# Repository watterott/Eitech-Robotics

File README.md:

# Eitech Robotics
Eitech Robotics is an Microchip SAMW25 based open-source robotics board.

* [Microchip ATSAMW25](http://www.microchip.com/wwwproducts/en/ATSAMW25) Module (SAM D21 ARM Cortex-M0+ and WINC1500 WiFi/WLAN SoC)
* USB CDC+MSC Bootloader (Arduino compatible)
* 5V tolerant IOs, UART, SPI, I2C
* 2x Dual Full-Bridge Motor Drivers (Allegro Micro A3909, up to 1A per Phase)
* 5V Switching Regulator (up to 2A)

## Hardware and Software
* [Schematics/Layout](https://github.com/watterott/Eitech-Robotics/tree/master/hardware)
* [Board Support Package for Arduino IDE](https://github.com/watterott/Eitech-Robotics/tree/master/arduino#eitech-board-support-package)
* [Driver for Windows](https://github.com/watterott/Eitech-Robotics/raw/master/arduino/driver.zip)

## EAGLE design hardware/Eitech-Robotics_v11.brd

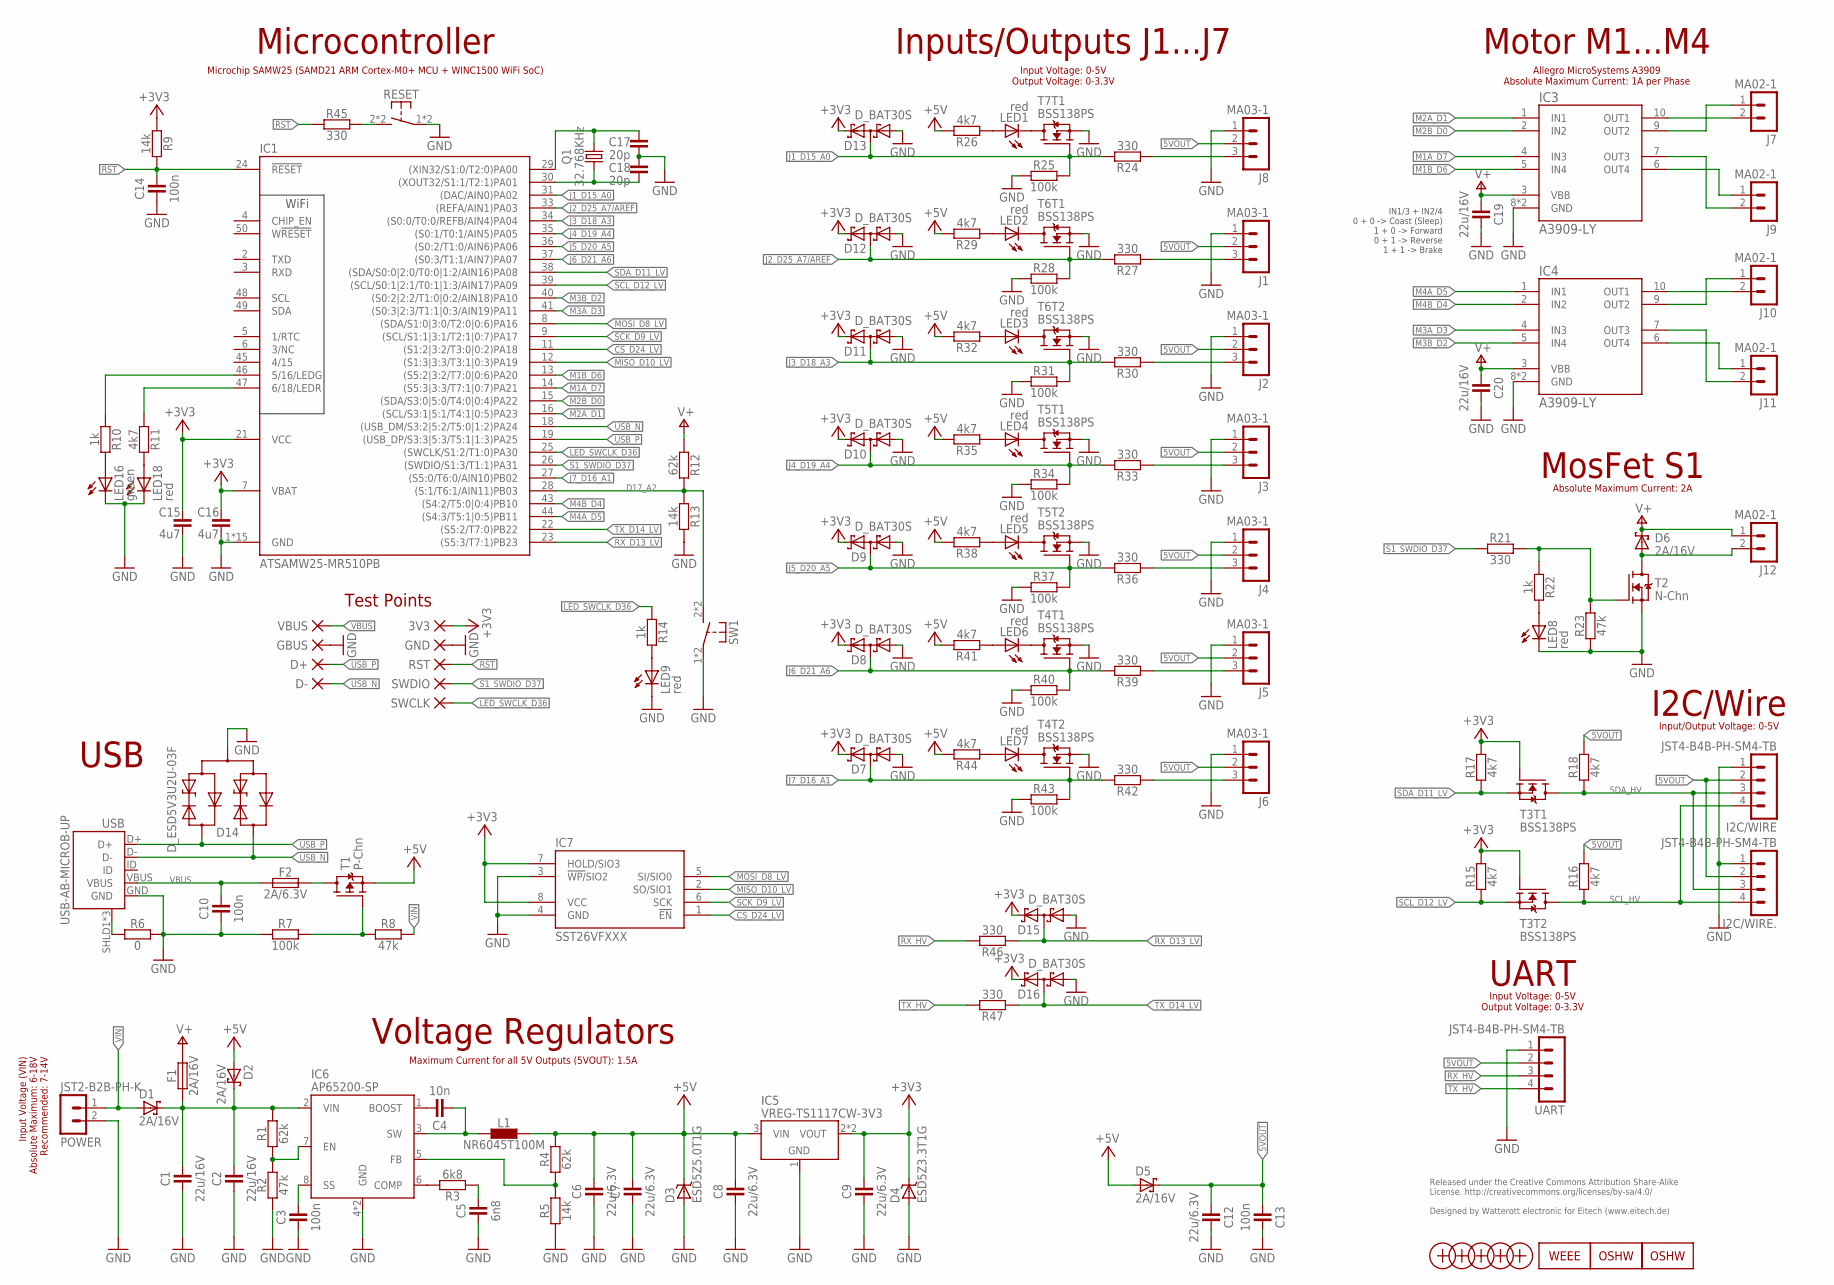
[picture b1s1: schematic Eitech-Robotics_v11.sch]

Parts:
3V3: PAD-1.0_NC
C1, C2, C19, C20: 22u/16V; C0805
C3, C10, C13, C14: 100n; C0402
C4: 10n; C0402
C5: 6n8; C0402
C6, C7, C8, C9, C12: 22u/6.3V; C0805
C15, C16: 4u7; C0603
C17, C18: 20p; C0402
D1, D2, D5, D6: 2A/16V; SOD123
D3: ESD5Z5.0T1G; SOD523
D4: ESD5Z3.3T1G; SOD523
D7, D8, D9, D10, D11, D12, D13, D15, D16: D_BAT30S; SOT323
D14: D_ESD5V3U2U-03F; SOT723
D+: PAD-1.0_NC
D-: PAD-1.0_NC
F1: 2A/16V; C1812
F2: 2A/6.3V; C1206
GBUS: PAD-1.0_NC
GND: PAD-1.0_NC
I2C/WIRE, I2C/WIRE.: JST4-B4B-PH-SM4-TB; JST_B4B-PH-SM4-TB
IC1: ATSAMW25-MR510PB; ATSAMW25-MRX10
IC3, IC4: A3909-LY; MSOP10-PAD
IC5: VREG-TS1117CW-3V3; SOT223
IC6: AP65200-SP; SO08-PAD
IC7: SST26VFXXX; SO08
J1, J2, J3, J4, J5, J6, J8: MA03-1
J7, J9, J10, J11, J12: MA02-1
L1: NR6045T100M; L_NR60XX
LED1, LED2, LED3, LED4, LED5, LED6, LED7, LED8, LED9, LED18: red; C0603
LED16: green; C0603
LOGO1: OSHW_LOGOX0100; OSHW_6X100
LOGO2: OSHW_LOGOX0150; OSHW_6X150
LOGO4: WEEE_LOGO-S; WEEE_TPLAC_S
POWER: JST2-B2B-PH-K; JST_B2B-PH-K
Q1: 32.768KHz; CRYSTAL_ZM315
R1, R4, R12: 62k; C0402
R2, R8, R23: 47k; C0402
R3: 6k8; C0402
R5, R9, R13: 14k; C0402
R6: 0; C0402
R7, R25, R28, R31, R34, R37, R40, R43: 100k; C0402
R10, R14, R22: 1k; C0402
R11, R15, R16, R17, R18, R26, R29, R32, R35, R38, R41, R44: 4k7; C0402
R21, R24, R27, R30, R33, R36, R39, R42, R45, R46, R47: 330; C0402
RESET: SW-TACTILE-TL3305C; TL3305; MPN TL3305C
RST: PAD-1.0_NC
SW1: SW-TACTILE-TL3305C; TL3305; MPN TL3305C
SWCLK: PAD-1.0_NC
SWDIO: PAD-1.0_NC
T1: P-Chn; SOT23
T2: N-Chn; SOT23
T3, T4, T5, T6, T7: BSS138PS; SOT363
UART: JST4-B4B-PH-SM4-TB; JST_B4B-PH-SM4-TB
USB: USB-AB-MICROB-UP; USB-MICROB-1051330011
VBUS: PAD-1.0_NC
X1, X2, X3, X4: PASSER-07; PASSER_07MM
X5: PASSER-04; PASSER_04MM

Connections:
5VOUT: C12.2, C13.2, D5.C, I2C/WIRE.2, I2C/WIRE..2, J1.2, J2.2, J3.2, J4.2, J5.2, J6.2, J8.2, R16.2, R18.2, UART.2
+3V3: 3V3.1, C9.2, C15.2, C16.2, D4.C, D7.2 (C), D8.2 (C), D9.2 (C), D10.2 (C), D11.2 (C), D12.2 (C), D13.2 (C), D15.2 (C), D16.2 (C), IC1.7 (VBAT), IC1.21 (VCC), IC5.2 (VOUT), IC5.4 (VOUT), IC7.7 (HOLD/SIO3), IC7.8 (VCC), R9.1, R15.2, R17.2, T3.2 (G), T3.5 (G)
+5V: C6.2, C7.2, C8.2, D2.A, D3.C, D5.A, IC5.3 (VIN), L1.2, R4.2, R26.2, R29.2, R32.2, R35.2, R38.2, R41.2, R44.2, T1.2 (S)
BOOST: C4.2, IC6.1 (BOOST)
COMP: IC6.6 (COMP), R3.2
CS_D24_LV: IC1.11 ((S1:2|3:2/T3:0|0:2)PA18), IC7.1 (!EN)
D17_A2: IC1.28 ((S:1/T6:1/AIN11)PB03), R12.2, R13.1, SW1.2 (S1), SW1.3 (S1)
GND: C1.1, C2.1, C3.1, C5.1, C6.1, C7.1, C8.1, C9.1, C10.1, C12.1, C13.1, C14.1, C15.1, C16.1, C17.2, C18.2, C19.2, C20.2, D3.A, D4.A, D7.1 (A), D8.1 (A), D9.1 (A), D10.1 (A), D11.1 (A), D12.1 (A), D13.1 (A), D14.3 (A), D15.1 (A), D16.1 (A), GBUS.1, GND.1, I2C/WIRE.1, I2C/WIRE..1, IC1.1 (GND), IC1.10 (GND), IC1.17 (GND), IC1.20 (GND), IC1.32 (GND), IC1.42 (GND), IC1.51 (GND), IC1.GND@1 (GND), IC1.GND@2 (GND), IC1.GND@3 (GND), IC1.GND@4 (GND), IC1.GND@5 (GND), IC1.GND@6 (GND), IC1.GND@7 (GND), IC1.GND@8 (GND), IC3.8 (GND), IC3.TP (GND), IC4.8 (GND), IC4.TP (GND), IC5.1 (GND), IC6.4 (GND), IC6.TP (GND), IC7.3 (!WP/!SIO2), IC7.4 (GND), J1.1, J2.1, J3.1, J4.1, J5.1, J6.1, J8.1, LED8.C, LED9.C, LED16.C, LED18.C, POWER.2, R2.1, R5.1, R6.1, R7.1, R13.2, R23.1, R25.1, R28.1, R31.1, R34.1, R37.1, R40.1, R43.1, RESET.1, RESET.4 (P1), SW1.1, SW1.4 (P1), T2.2 (S), T4.1 (S), T4.4 (S), T5.1 (S), T5.4 (S), T6.1 (S), T6.4 (S), T7.1 (S), UART.1, USB.GND
IO16: IC1.46 (5/16/LEDG), R10.1
IO18: IC1.47 (6/18/LEDR), R11.1
J1_D15_A0: D13.3 (CA), IC1.31 ((DAC/AIN0)PA02), R24.2, R25.2, T7.2 (G)
J2_D25_A7/AREF: D12.3 (CA), IC1.33 ((REFA/AIN1)PA03), R27.2, R28.2, T6.2 (G)
J3_D18_A3: D11.3 (CA), IC1.34 ((S0:0/T0:0/REFB/AIN4)PA04), R30.2, R31.2, T6.5 (G)
J4_D19_A4: D10.3 (CA), IC1.35 ((S0:1/T0:1/AIN5)PA05), R33.2, R34.2, T5.2 (G)
J5_D20_A5: D9.3 (CA), IC1.36 ((S0:2/T1:0/AIN6)PA06), R36.2, R37.2, T5.5 (G)
J6_D21_A6: D8.3 (CA), IC1.37 ((S0:3/T1:1/AIN7)PA07), R39.2, R40.2, T4.2 (G)
J7_D16_A1: D7.3 (CA), IC1.27 ((S5:0/T6:0/AIN10)PB02), R42.2, R43.2, T4.5 (G)
LED_SWCLK_D36: IC1.25 ((SWCLK/S1:2/T1:0)PA30), R14.1, SWCLK.1
M1A_D7: IC1.14 ((S5:3|3:3/T7:1|0:7)PA21), IC3.4 (IN3)
M1B_D6: IC1.13 ((S5:2|3:2/T7:0|0:6)PA20), IC3.5 (IN4)
M1_O1: IC3.7 (OUT3), J9.2
M1_O2: IC3.6 (OUT4), J9.1
M2A_D1: IC1.16 ((SCL/S3:1|5:1/T4:1|0:5)PA23), IC3.1 (IN1)
M2B_D0: IC1.15 ((SDA/S3:0|5:0/T4:0|0:4)PA22), IC3.2 (IN2)
M2_O1: IC3.10 (OUT1), J7.2
M2_O2: IC3.9 (OUT2), J7.1
M3A_D3: IC1.41 ((S0:3|2:3/T1:1|0:3/AIN19)PA11), IC4.4 (IN3)
M3B_D2: IC1.40 ((S0:2|2:2/T1:0|0:2/AIN18)PA10), IC4.5 (IN4)
M3_O1: IC4.7 (OUT3), J11.2
M3_O2: IC4.6 (OUT4), J11.1
M4A_D5: IC1.44 ((S4:3/T5:1|0:5)PB11), IC4.1 (IN1)
M4B_D4: IC1.43 ((S4:2/T5:0|0:4)PB10), IC4.2 (IN2)
M4_O1: IC4.10 (OUT1), J10.2
M4_O2: IC4.9 (OUT2), J10.1
MISO_D10_LV: IC1.12 ((S1:3|3:3/T3:1|0:3)PA19), IC7.2 (SO/SIO1)
MOSI_D8_LV: IC1.8 ((SDA/S1:0|3:0/T2:0|0:6)PA16), IC7.5 (SI/SIO0)
unnamed: LED8.A, R22.2
unnamed: J8.3, R24.1
unnamed: F2.2, T1.3 (D)
unnamed: R7.2, R8.1, T1.1 (G)
unnamed: LED9.A, R14.2
unnamed: R21.2, R22.1, R23.2, T2.1 (G)
unnamed: LED7.C, T4.3 (D)
unnamed: LED7.A, R44.1
unnamed: J6.3, R42.1
unnamed: C4.1, IC6.3 (SW), L1.1
unnamed: C3.2, IC6.8 (SS)
unnamed: J5.3, R39.1
unnamed: J4.3, R36.1
unnamed: J3.3, R33.1
unnamed: IC6.5 (FB), R4.1, R5.2
unnamed: LED6.C, T4.6 (D)
unnamed: LED6.A, R41.1
unnamed: J1.3, R27.1
unnamed: LED5.A, R38.1
unnamed: J2.3, R30.1
unnamed: LED4.A, R35.1
unnamed: LED4.C, T5.6 (D)
unnamed: LED5.C, T5.3 (D)
unnamed: LED3.A, R32.1
unnamed: LED2.A, R29.1
unnamed: LED2.C, T6.6 (D)
unnamed: LED3.C, T6.3 (D)
unnamed: LED1.A, R26.1
unnamed: LED1.C, T7.6 (D)
unnamed: C5.2, R3.1
unnamed: IC6.7 (EN), R1.1, R2.2
unnamed: LED18.A, R11.2
unnamed: LED16.A, R10.2
RST: C14.2, IC1.24 (!RESET), R9.2, R45.1, RST.1
RST_SW: R45.2, RESET.2 (S1), RESET.3 (S1)
RX_D13_LV: D15.3 (CA), IC1.23 ((S5:3/T7:1)PB23), R46.1
RX_HV: R46.2, UART.3
S1: D6.A, J12.2, T2.3 (D)
S1_SWDIO_D37: IC1.26 ((SWDIO/S1:3/T1:1)PA31), R21.1, SWDIO.1
SCK_D9_LV: IC1.9 ((SCL/S1:1|3:1/T2:1|0:7)PA17), IC7.6 (SCK)
SCL_D12_LV: IC1.39 ((SCL/S0:1|2:1/T0:1|1:3/AIN17)PA09), R15.1, T3.4 (S)
SCL_HV: I2C/WIRE.4, I2C/WIRE..4, R16.1, T3.3 (D)
SDA_D11_LV: IC1.38 ((SDA/S0:0|2:0/T0:0|1:2/AIN16)PA08), R17.1, T3.1 (S)
SDA_HV: I2C/WIRE.3, I2C/WIRE..3, R18.1, T3.6 (D)
SHLD1: R6.2, USB.SHLD1 (SHIELD), USB.SHLD2 (SHIELD), USB.SHLD3 (SHIELD)
TX_D14_LV: D16.3 (CA), IC1.22 ((S5:2/T7:0)PB22), R47.1
TX_HV: R47.2, UART.4
USB_N: D14.1 (C1), D-.1, IC1.18 ((USB_DM/S3:2|5:2/T5:0|1:2)PA24), USB.D-
USB_P: D14.2 (C2), D+.1, IC1.19 ((USB_DP/S3:3|5:3/T5:1|1:3)PA25), USB.D+
V+: C19.1, C20.1, D6.C, F1.2, IC3.3 (VBB), IC4.3 (VBB), J12.1, R12.1
VBUS: C10.2, F2.1, USB.VBUS, VBUS.1
VIN: D1.A, POWER.1, R8.2
VINP: C1.2, C2.2, D1.C, D2.C, F1.1, IC6.2 (VIN), R1.2
XIN: C17.1, IC1.29 ((XIN32/S1:0/T2:0)PA00), Q1.2
XOUT: C18.1, IC1.30 ((XOUT32/S1:1/T2:1)PA01), Q1.1

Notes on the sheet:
USB
Motor M1...M4
MosFet S1
I2C/Wire
UART
Inputs/Outputs J1...J7
Voltage Regulators
Microcontroller
Test Points
Released under the Creative Commons Attribution Share-Alike License. http://creativecommons.org/licenses/by-sa/4.0/ Designed by Watterott electronic for Eitech (www.eitech.de)
Input Voltage (VIN) Absolute Maximum: 6-18V Recommended: 7-14V
Input Voltage: 0-5V Output Voltage: 0-3.3V
Allegro MicroSystems A3909 Absolute Maximum Current: 1A per Phase
Input/Output Voltage: 0-5V
Absolute Maximum Current: 2A
Microchip SAMW25 (SAMD21 ARM Cortex-M0+ MCU + WINC1500 WiFi SoC)
Maximum Current for all 5V Outputs (5VOUT): 1.5A
IN1/3 + IN2/4 0 + 0 -> Coast (Sleep) 1 + 0 -> Forward 0 + 1 -> Reverse 1 + 1 -> Brake

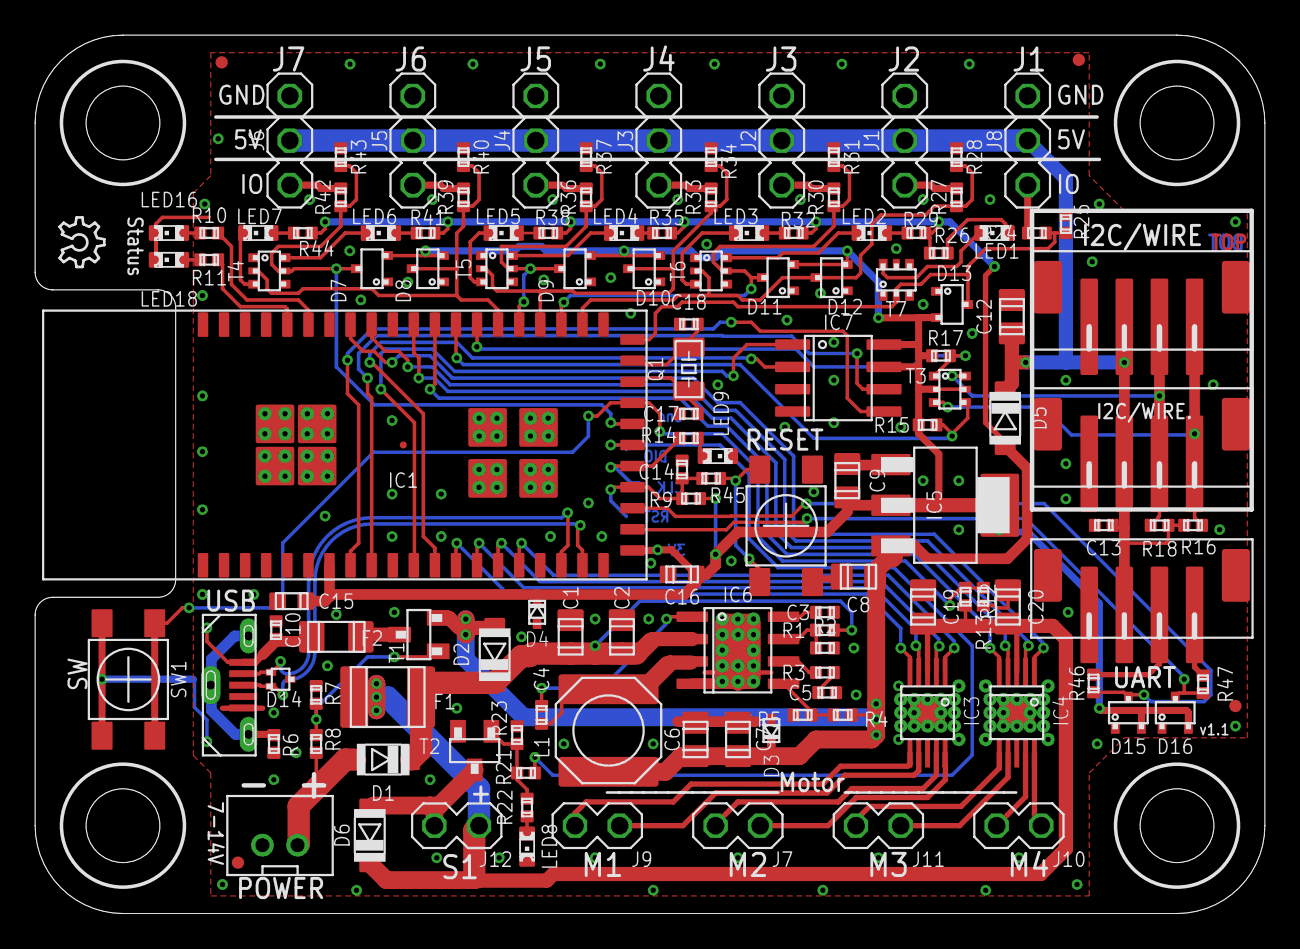
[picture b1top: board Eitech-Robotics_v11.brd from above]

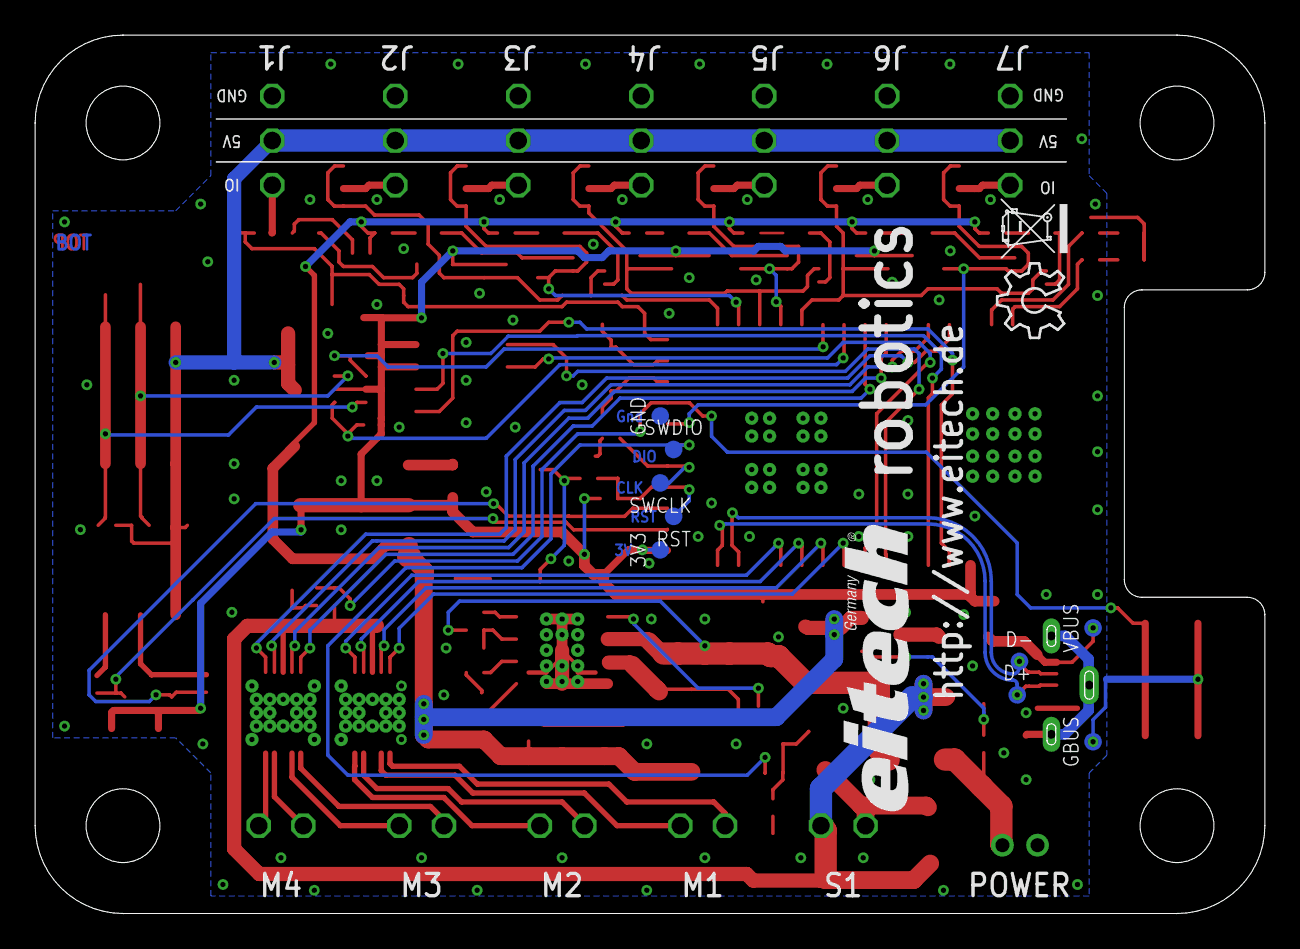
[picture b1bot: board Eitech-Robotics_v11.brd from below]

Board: 2 copper layers, 70.0 x 50.0 mm, 144 parts (11 on the bottom side), 91 nets.

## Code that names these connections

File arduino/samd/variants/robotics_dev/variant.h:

/*
  Copyright (c) 2014-2015 Arduino LLC.  All right reserved.

  This library is free software; you can redistribute it and/or
  modify it under the terms of the GNU Lesser General Public
  License as published by the Free Software Foundation; either
  version 2.1 of the License, or (at your option) any later version.

  This library is distributed in the hope that it will be useful,
  but WITHOUT ANY WARRANTY; without even the implied warranty of
  MERCHANTABILITY or FITNESS FOR A PARTICULAR PURPOSE.
  See the GNU Lesser General Public License for more details.

  You should have received a copy of the GNU Lesser General Public
  License along with this library; if not, write to the Free Software
  Foundation, Inc., 51 Franklin St, Fifth Floor, Boston, MA  02110-1301  USA
*/

#pragma once

// The definitions here needs a SAMD core >=1.6.10
#define ARDUINO_SAMD_VARIANT_COMPLIANCE 10610

#include <WVariant.h>

// General definitions
// -------------------

// Frequency of the board main oscillator
#define VARIANT_MAINOSC (32768ul)

// Master clock frequency
#define VARIANT_MCK     (48000000ul)

// Pins
// ----

// Robotics J1...J7
#define RJ1   (15u) // PA02: D15 / A0
#define RJ2   (25u) // PA03: D25 / A7/AREF
#define RJ3   (18u) // PA04: D18 / A3
#define RJ4   (19u) // PA05: D19 / A4
#define RJ5   (20u) // PA06: D20 / A5
#define RJ6   (21u) // PA07: D21 / A6
#define RJ7   (16u) // PB02: D16 / A1
// Robotics M1...M4
#define RM1A   (7u) // PA21: D7
#define RM1B   (6u) // PA20: D6
#define RM2A   (1u) // PA23: D1
#define RM2B   (0u) // PA22: D0
#define RM3A   (3u) // PA11: D3
#define RM3B   (2u) // PA10: D2
#define RM4A   (5u) // PB11: D5
#define RM4B   (4u) // PB10: D4
#define RVBB  (17u) // PB3: D17 / A2
// Robotics S1
#define RS1   (36u) // PA31 / SWDIO (Dev-Edition: PA30 / SWCLK)

// Number of pins defined in PinDescription array
#define PINS_COUNT           (26u) // 26
#define NUM_DIGITAL_PINS     (22u) // 22
#define NUM_ANALOG_INPUTS    (7u)  // 7
#define NUM_ANALOG_OUTPUTS   (1u)  // 1
#define analogInputToDigitalPin(p)  ((p < 7u) ? (p) + 15u : -1)

// Low-level pin register query macros
// -----------------------------------
#define digitalPinToPort(P)      (&(PORT->Group[g_APinDescription[P].ulPort]))
#define digitalPinToBitMask(P)   (1 << g_APinDescription[P].ulPin)
//#define analogInPinToBit(P)    ()
#define portOutputRegister(port) (&(port->OUT.reg))
#define portInputRegister(port)  (&(port->IN.reg))
#define portModeRegister(port)   (&(port->DIR.reg))
#define digitalPinHasPWM(P)      (g_APinDescription[P].ulPWMChannel != NOT_ON_PWM || g_APinDescription[P].ulTCChannel != NOT_ON_TIMER)

/*
 * digitalPinToTimer(..) is AVR-specific and is not defined for SAMD
 * architecture. If you need to check if a pin supports PWM you must
 * use digitalPinHasPWM(..).
 *
 * https://github.com/arduino/Arduino/issues/1833
 */
// #define digitalPinToTimer(P)

// LEDs
// ----
#define PIN_LED     (37u) // PA30 / SWCLK (Dev-Edition: PA31 / SWDIO)
#define LED_BUILTIN PIN_LED

// Analog pins
// -----------
#define PIN_A0   (15u)
#define PIN_A1   (16u)
#define PIN_A2   (17u)
#define PIN_A3   (18u)
#define PIN_A4   (19u)
#define PIN_A5   (20u)
#define PIN_A6   (21u)
#define PIN_A7   (25u)
#define PIN_DAC0 (15u)

static const uint8_t A0   = PIN_A0;
static const uint8_t A1   = PIN_A1;
static const uint8_t A2   = PIN_A2;
static const uint8_t A3   = PIN_A3;
static const uint8_t A4   = PIN_A4;
static const uint8_t A5   = PIN_A5;
static const uint8_t A6   = PIN_A6;
static const uint8_t A7   = PIN_A7;
static const uint8_t DAC0 = PIN_DAC0;
#define ADC_RESOLUTION 12

// SPI Interfaces
// --------------
#define SPI_INTERFACES_COUNT 2

// SPI
#define PIN_SPI_MISO  (10u)
#define PIN_SPI_MOSI  (8u)
#define PIN_SPI_SCK   (9u)
#define PIN_SPI_SS    (24u)
#define PERIPH_SPI    sercom1
#define PAD_SPI_TX    SPI_PAD_0_SCK_1
#define PAD_SPI_RX    SERCOM_RX_PAD_3
static const uint8_t SS   = PIN_SPI_SS;   // SPI Slave SS not used. Set here only for reference.
static const uint8_t MOSI = PIN_SPI_MOSI;
static const uint8_t MISO = PIN_SPI_MISO;
static const uint8_t SCK  = PIN_SPI_SCK;

// SPI1: Connected to WINC1501B
#define PIN_SPI1_MISO (29u)
#define PIN_SPI1_MOSI (26u)
#define PIN_SPI1_SCK  (27u)
#define PIN_SPI1_SS   (28u)
#define PERIPH_SPI1   sercom2
#define PAD_SPI1_TX   SPI_PAD_0_SCK_1
#define PAD_SPI1_RX   SERCOM_RX_PAD_3
static const uint8_t SS1   = PIN_SPI1_SS;
static const uint8_t MOSI1 = PIN_SPI1_MOSI;
static const uint8_t MISO1 = PIN_SPI1_MISO;
static const uint8_t SCK1  = PIN_SPI1_SCK;

// Wire Interfaces
// ---------------
#define WIRE_INTERFACES_COUNT 1

// Wire
#define PIN_WIRE_SDA        (11u)
#define PIN_WIRE_SCL        (12u)
#define PERIPH_WIRE         sercom0
#define WIRE_IT_HANDLER     SERCOM0_Handler
static const uint8_t SDA = PIN_WIRE_SDA;
static const uint8_t SCL = PIN_WIRE_SCL;

// USB
// ---
#define PIN_USB_DM          (22u)
#define PIN_USB_DP          (23u)
#define PIN_USB_HOST_ENABLE (-1)

// Needed for WINC1501B (WiFi101) library
// --------------------------------------
#define WINC1501_RESET_PIN   (30u)
#define WINC1501_CHIP_EN_PIN (31u)
#define WINC1501_INTN_PIN    (33u)
#define WINC1501_SPI         SPI1
#define WINC1501_SPI_CS_PIN  PIN_SPI1_SS


// Serial ports
// ------------
#ifdef __cplusplus
#include "SERCOM.h"
#include "Uart.h"

// Instances of SERCOM
extern SERCOM sercom0;
extern SERCOM sercom1;
extern SERCOM sercom2;
extern SERCOM sercom3;
extern SERCOM sercom4;
extern SERCOM sercom5;

// Serial1
extern Uart Serial1;
#define PIN_SERIAL1_RX (13u)
#define PIN_SERIAL1_TX (14u)
#define PAD_SERIAL1_TX (UART_TX_PAD_2)
#define PAD_SERIAL1_RX (SERCOM_RX_PAD_3)
#endif // __cplusplus

// These serial port names are intended to allow libraries and architecture-neutral
// sketches to automatically default to the correct port name for a particular type
// of use.  For example, a GPS module would normally connect to SERIAL_PORT_HARDWARE_OPEN,
// the first hardware serial port whose RX/TX pins are not dedicated to another use.
//
// SERIAL_PORT_MONITOR        Port which normally prints to the Arduino Serial Monitor
//
// SERIAL_PORT_USBVIRTUAL     Port which is USB virtual serial
//
// SERIAL_PORT_LINUXBRIDGE    Port which connects to a Linux system via Bridge library
//
// SERIAL_PORT_HARDWARE       Hardware serial port, physical RX & TX pins.
//
// SERIAL_PORT_HARDWARE_OPEN  Hardware serial ports which are open for use.  Their RX & TX
//                            pins are NOT connected to anything by default.
#define SERIAL_PORT_USBVIRTUAL      SerialUSB
#define SERIAL_PORT_MONITOR         SerialUSB
#define SERIAL_PORT_HARDWARE        Serial1
#define SERIAL_PORT_HARDWARE_OPEN   Serial1

// Alias Serial to SerialUSB
#define Serial                      SerialUSB

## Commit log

2017-10-22 updated pin info
2017-12-02 updated schematics
2017-12-02 updated BSP and WiFi101 lib
2018-03-02 updated bootloader and bsp
2019-02-11 updated libs
2019-02-11 added rev 1.1
2019-02-11 updated bsp
2019-04-13 updated bootloader
